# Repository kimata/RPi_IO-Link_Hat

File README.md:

# Raspberry Pi IO-LINK Hat

## 概要

Raspberry Pi と IO-Link 基板を接続するためのブリッジ基板です．

24V 電源で動作し，IO-Link 機器と Raspberry Pi への電源の供給を行います．

## 使用部品

使用している主な部品は以下の通りです．

| リファレンス | Mouser #             |
| ------------ | -------------------- |
| D3           | 512-S100             |
| D4, D5       | 755-PTZTFTE2536B     |
| J1           | 490-PJ-063AH         |
| L1           | 810-SPM5030VT-2R2M-D |
| Q2, Q3       | 757-T2N7002BKLM      |
| Q4           | 512-FQT7N10LTF       |
| U1           | 584-LT8609AJDDM-5#TR |
| U2           | 584-LTC2874IFE#PBF   |

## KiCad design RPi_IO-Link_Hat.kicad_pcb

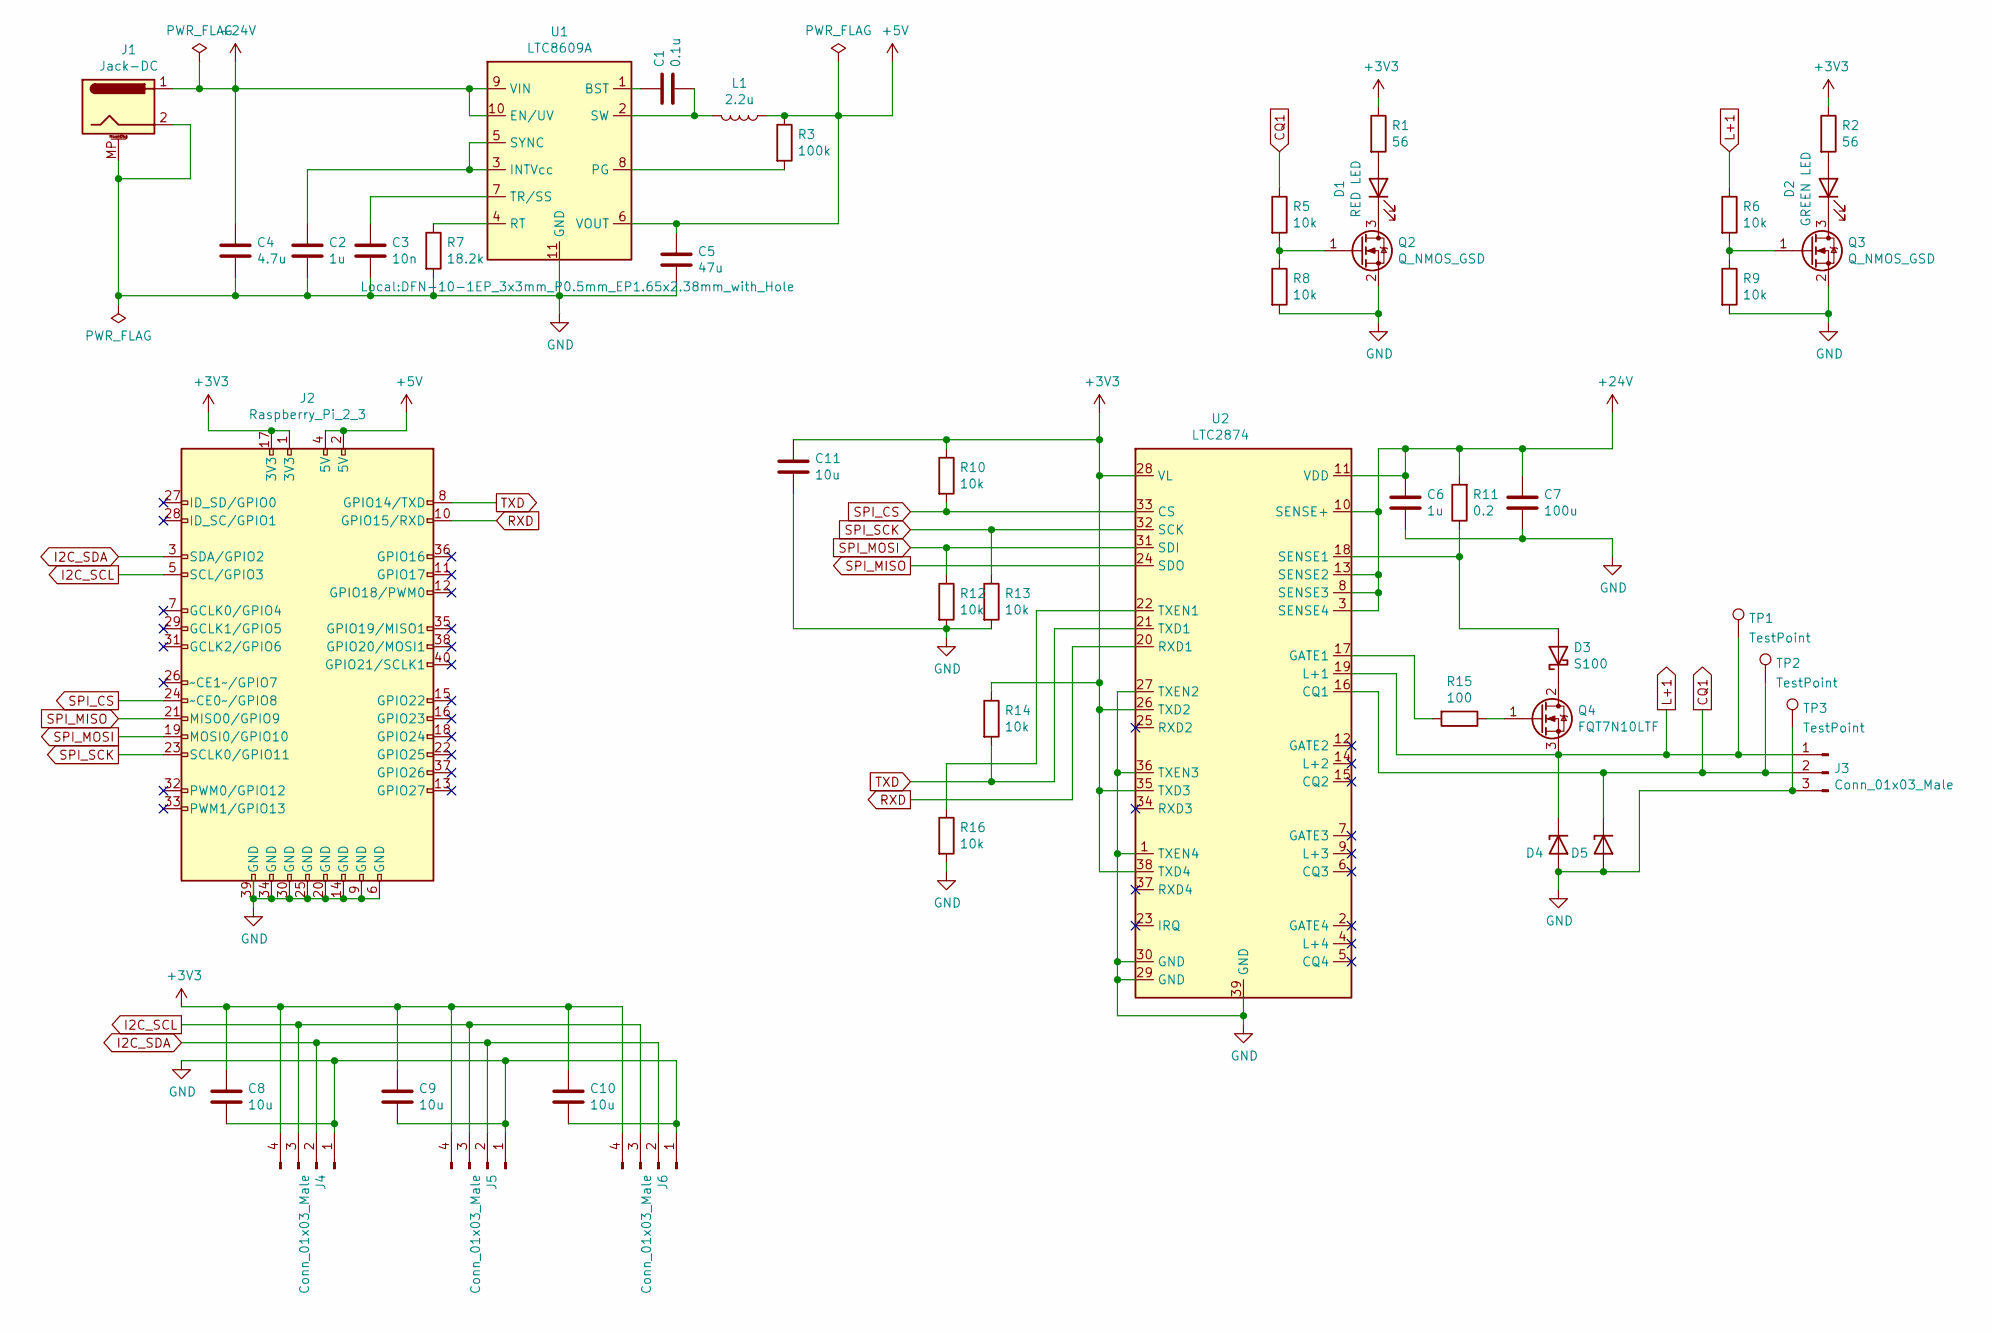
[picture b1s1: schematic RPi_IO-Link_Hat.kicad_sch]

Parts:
C1: 0.1u; C_0805_2012Metric_Pad1.18x1.45mm_HandSolder; Mouser 81-GCJ21BL81H104KA1L
C2: 1u; C_0805_2012Metric_Pad1.18x1.45mm_HandSolder; Mouser 81-GRM219R61A105MA1D
C3: 10n; C_0805_2012Metric_Pad1.18x1.45mm_HandSolder; Mouser 81-GCJ216R71E103KA1D
C4: 4.7u; C_1206_3216Metric_Pad1.33x1.80mm_HandSolder; Mouser 81-GRM31CR71H475KA2K
C5: 47u; C_0805_2012Metric_Pad1.18x1.45mm_HandSolder; Mouser 81-GRT21BR60J476ME3L
C6: 1u; C_1206_3216Metric_Pad1.33x1.80mm_HandSolder; Mouser 81-GRT31MC81H105KE1L
C7: 100u; CP_Radial_D8.0mm_P3.50mm; Mouser 667-EEU-EB1H101SJ
C8, C9, C10, C11: 10u; C_0805_2012Metric_Pad1.18x1.45mm_HandSolder; Mouser 81-GRM219R60J106KE9D
D1: RED LED; LED_0805_2012Metric_Pad1.15x1.40mm_HandSolder; Mouser 720-LGR971-KN-1
D2: GREEN LED; LED_0805_2012Metric_Pad1.15x1.40mm_HandSolder; Mouser 720-LSR976-NR-1
D3: S100; D_SMA_Handsoldering; Mouser 512-S100
D4, D5: PTZTFTE2536B; D_SMA_Handsoldering; Mouser 755-PTZTFTE2536B
J1: Jack-DC; BarrelJack_CUI_PJ-063AH_Horizontal; Mouser 490-PJ-063AH
J2: Raspberry_Pi_2_3; PinSocket_2x20_P2.54mm_Vertical
J3: Conn_01x03_Male; JST_EH_B3B-EH-A_1x03_P2.50mm_Vertical
J4, J5, J6: Conn_01x03_Male; JST_EH_B4B-EH-A_1x04_P2.50mm_Vertical
L1: 2.2u; L_TDK_SPM5030VT; Mouser 810-SPM5030VT-2R2M-D
Q2, Q3: Q_NMOS_GSD; SOT-23; Mouser 757-T2N7002BKLM
Q4: FQT7N10LTF; SOT-223-3_TabPin2_empty; Mouser 512-FQT7N10LTF
R1, R2: 56; R_0805_2012Metric_Pad1.20x1.40mm_HandSolder; Mouser 667-ERJ-6ENF56R0V
R3: 100k; R_0805_2012Metric_Pad1.20x1.40mm_HandSolder; Mouser 667-ERJ-6GEYJ104V
R5, R6, R8, R9, R10, R12, R13, R14, R16: 10k; R_0805_2012Metric_Pad1.20x1.40mm_HandSolder; Mouser 667-ERJ-6ENF1002V
R7: 18.2k; R_0805_2012Metric_Pad1.20x1.40mm_HandSolder; Mouser 667-ERJ-6ENF1822V
R11: 0.2; R_0805_2012Metric_Pad1.20x1.40mm_HandSolder; Mouser 667-ERJ-6BSFR20V
R15: 100; R_0805_2012Metric_Pad1.20x1.40mm_HandSolder; Mouser 667-ERJ-6ENF1000V
TP1, TP2, TP3: TestPoint; TestPoint_Loop_D1.80mm_Drill1.0mm_Beaded
U1: LTC8609A; DFN-10-1EP_3x3mm_P0.5mm_EP1.65x2.38mm_with_Hole; Mouser 584-LT8609AJDDM-5#TR
U2: LTC2874; TSSOP-38_4.4x9.7mm_P0.5mm_with_Hole; Mouser 584-LTC2874IFE#PBF

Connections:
+3V3: C8.1, C9.1, C10.1, C11.1, J2.1 (3V3), J2.17 (3V3), J4.4, J5.4, J6.4, R1.1, R2.1, R10.1, R14.1, U2.26 (TXD2), U2.28 (VL), U2.35 (TXD3), U2.38 (TXD4)
+5V: C5.1, J2.2 (5V), J2.4 (5V), L1.1, R3.1, U1.6 (VOUT)
+24V: C4.1, C6.1, C7.1, J1.1, R11.2, U1.9 (VIN), U1.10 (EN/UV), U2.3 (SENSE4), U2.8 (SENSE3), U2.10 (SENSE+), U2.11 (VDD), U2.13 (SENSE2)
CQ1: D5.1 (K), J3.2, R5.1, TP2.1, U2.16 (CQ1)
GND: C2.2, C3.2, C4.2, C5.2, C6.2, C7.2, C8.2, C9.2, C10.2, C11.2, D4.2 (A), D5.2 (A), J1.2, J1.MP (MountPin), J2.6 (GND), J2.9 (GND), J2.14 (GND), J2.20 (GND), J2.25 (GND), J2.30 (GND), J2.34 (GND), J2.39 (GND), J3.3, J4.1, J5.1, J6.1, Q2.2 (S), Q3.2 (S), R7.2, R8.2, R9.2, R12.2, R13.2, R16.2, TP3.1, U1.11 (GND), U2.1 (TXEN4), U2.27 (TXEN2), U2.29 (GND), U2.30 (GND), U2.36 (TXEN3), U2.39 (GND)
I2C_SCL: J2.5 (SCL/GPIO3), J4.3, J5.3, J6.3
I2C_SDA: J2.3 (SDA/GPIO2), J4.2, J5.2, J6.2
L+1: D4.1 (K), J3.1, Q4.3 (S), R6.1, TP1.1, U2.19 (L+1)
unnamed: C1.1, U1.1 (BST)
unnamed: C1.2, L1.2, U1.2 (SW)
unnamed: C2.1, U1.3 (INTVcc), U1.5 (SYNC)
unnamed: C3.1, U1.7 (TR/SS)
unnamed: D1.1 (K), Q2.3 (D)
unnamed: D1.2 (A), R1.2
unnamed: D2.1 (K), Q3.3 (D)
unnamed: D2.2 (A), R2.2
unnamed: D3.1 (K), Q4.2 (D)
unnamed: D3.2 (A), R11.1, U2.18 (SENSE1)
unnamed: Q2.1 (G), R5.2, R8.1
unnamed: Q3.1 (G), R6.2, R9.1
unnamed: Q4.1 (G), R15.1
unnamed: R3.2, U1.8 (PG)
unnamed: R7.1, U1.4 (RT)
unnamed: R15.2, U2.17 (GATE1)
unnamed: R16.1, U2.22 (TXEN1)
RXD: J2.10 (GPIO15/RXD), U2.20 (RXD1)
SPI_CS: J2.24 (~CE0~/GPIO8), R10.2, U2.33 (CS)
SPI_MISO: J2.21 (MISO0/GPIO9), U2.24 (SDO)
SPI_MOSI: J2.19 (MOSI0/GPIO10), R12.1, U2.31 (SDI)
SPI_SCK: J2.23 (SCLK0/GPIO11), R13.1, U2.32 (SCK)
TXD: J2.8 (GPIO14/TXD), R14.2, U2.21 (TXD1)

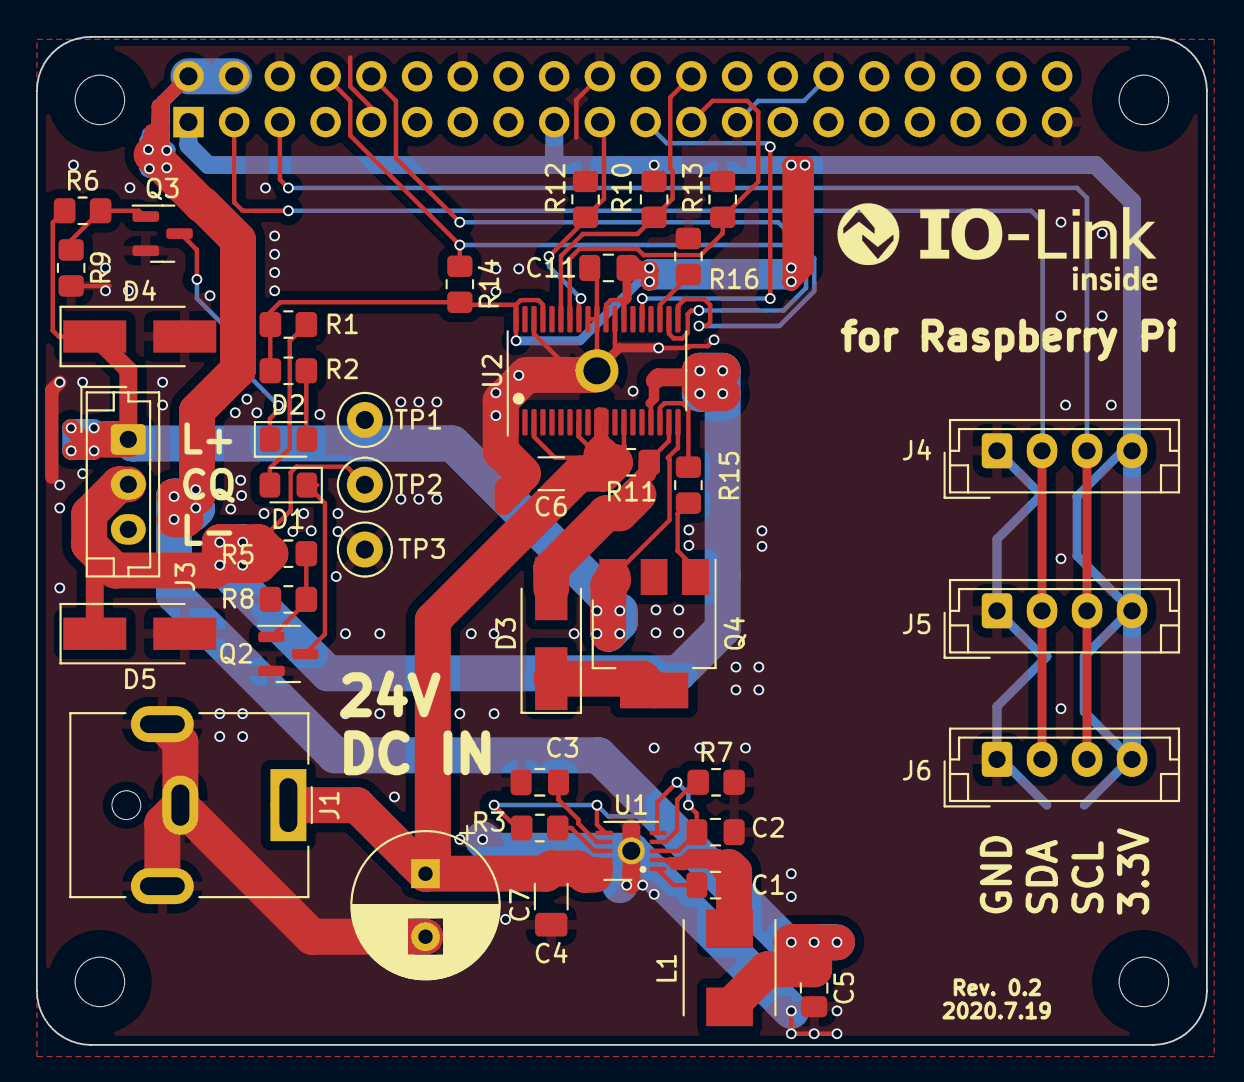
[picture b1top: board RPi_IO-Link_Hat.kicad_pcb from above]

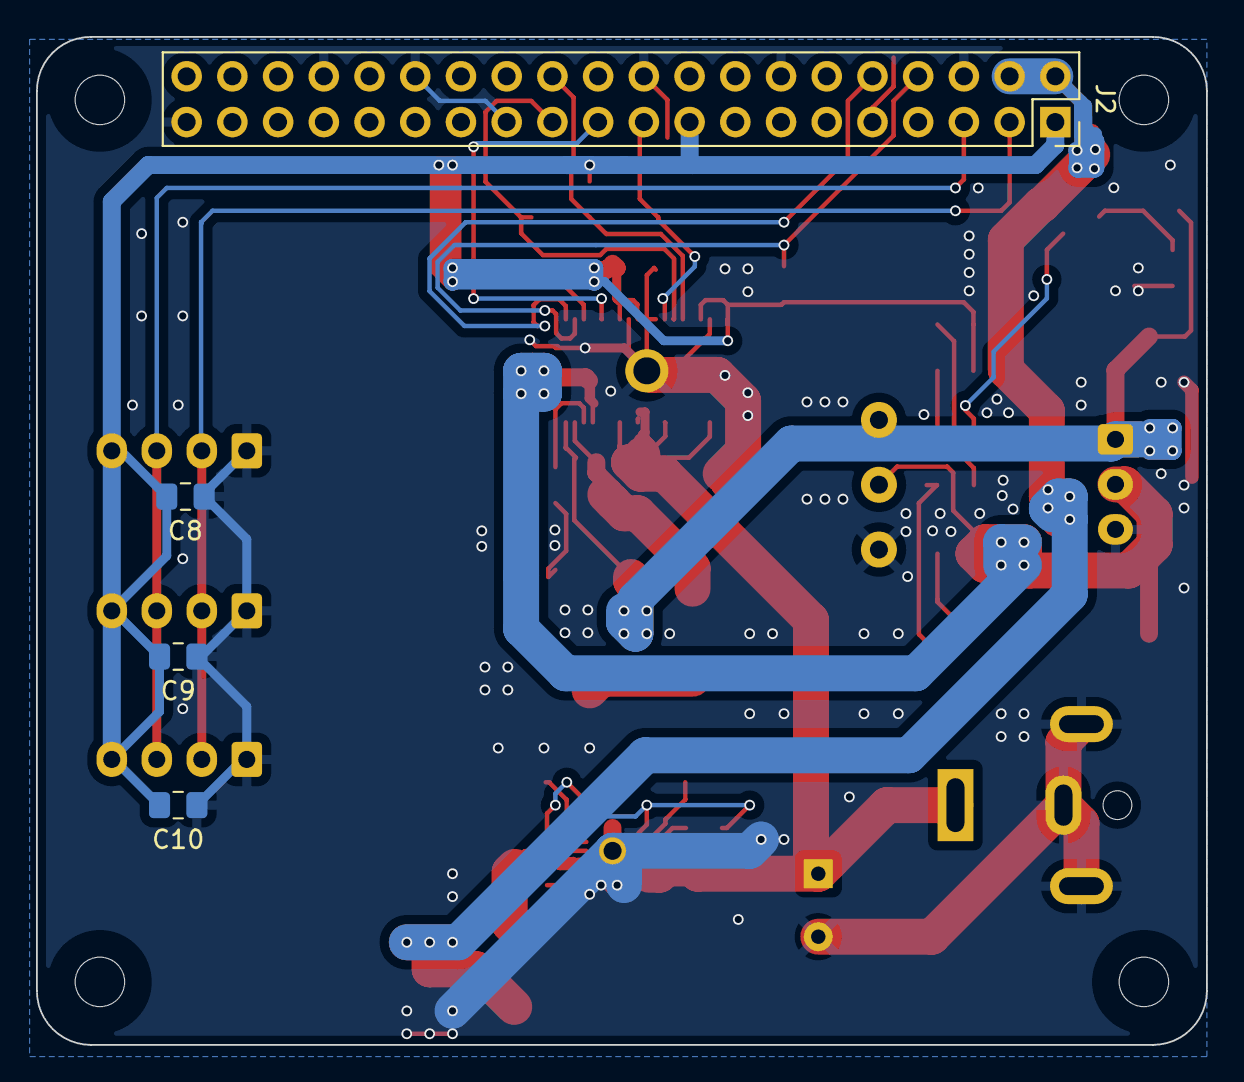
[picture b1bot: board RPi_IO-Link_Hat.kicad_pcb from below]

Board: 2 copper layers, 65.0 x 56.0 mm, 46 parts (4 on the bottom side), 31 nets.

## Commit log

2021-07-04 feat: とりあえず完成
2021-07-04 fix: KiCad 5.99 に移行
2021-07-04 fix: Mouser に在庫がある部品に置き換え
2021-07-04 fix: ライブラリの参照がおかしくなっていた問題を修正
2021-07-04 fix: KiCad 5.99 に追従
2021-07-04 fix: 電流検出抵抗を 2012 サイズに変更
2021-07-05 fix: 名前を変更
2021-07-11 fix: ライブラリパスの設定を追加
2021-07-19 fix: 改善 - CQ H で LED を点灯させるようにした - TP を追加
2021-08-11 fix: 手はんだしやすくするため，LTC8609A のランドサイズを少し拡大
2021-08-11 feat: 基板製造用のファイルを登録
2021-08-11 doc: ドキュメントを追加
